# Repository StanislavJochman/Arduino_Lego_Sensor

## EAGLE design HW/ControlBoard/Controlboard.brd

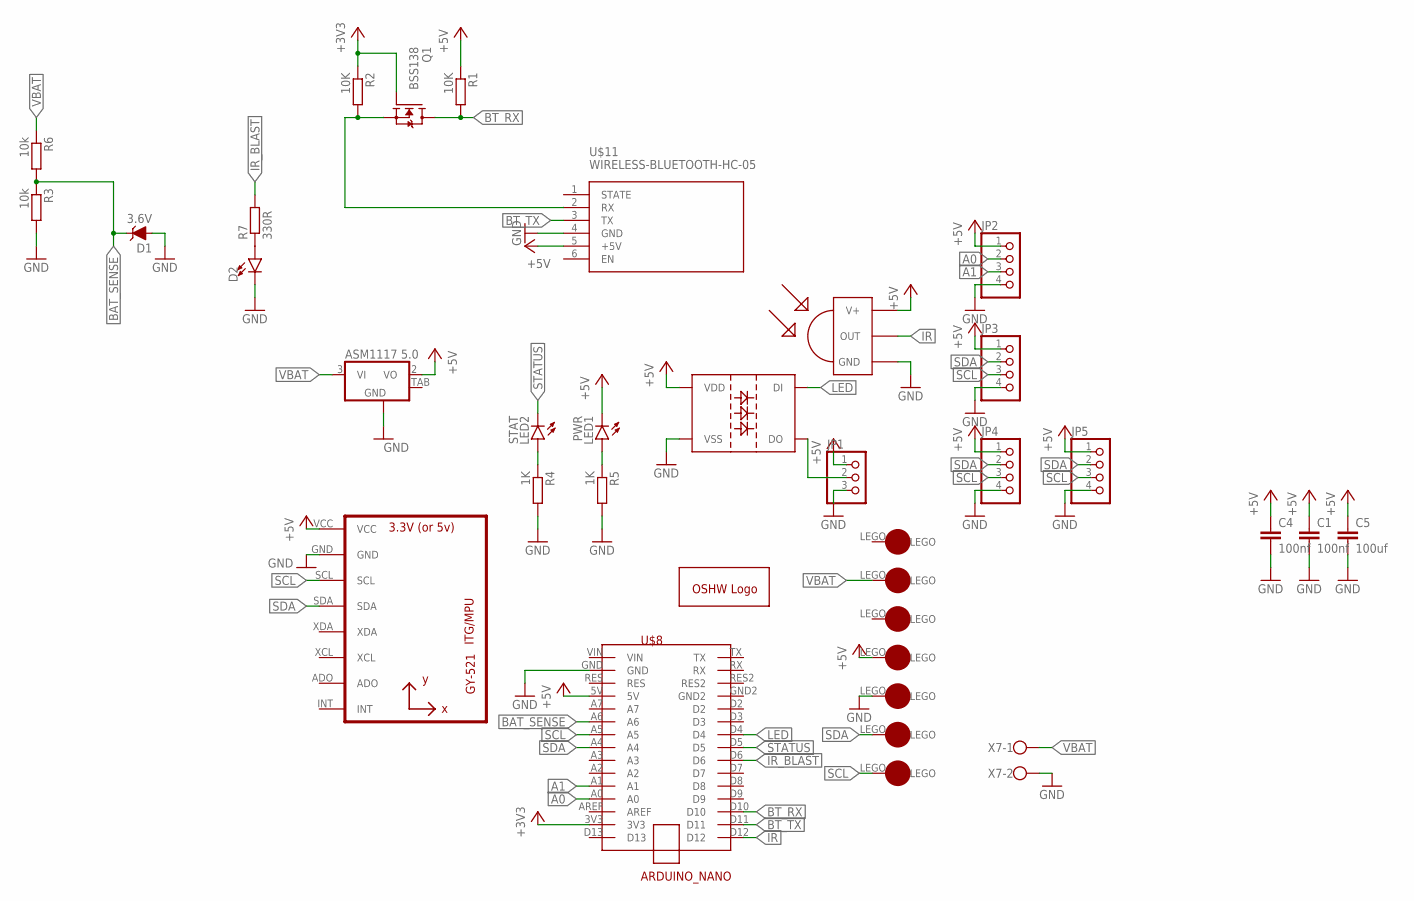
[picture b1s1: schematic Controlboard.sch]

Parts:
C1, C4: 100nf; C1206
C5: 100uf; C1206
D1: 3.6V; SOD-323
D2: LED5MM; LED_5MM
JP1: PINHD-1X3; 1X03
JP2, JP3, JP4, JP5: PINHD-1X4; 1X04
LED1: PWR; 1206
LED2: STAT; 1206
LED3: IND; WS2812B
Q1: BSS138; SOT23
R1, R2: 10K; M1206
R3, R6: 10k; M1206
R4, R5: 1K; M1206
R7: 330R; M1206
U1: MPU-6050MPU6050; MPU-6050
U$1, U$3, U$4, U$5, U$6, U$7, U$9: LEGO-1X1
U$2: OPENSOURCE; OSHW_5MM
U$8: ARDUINO_NANO; ARDUIN_NANO
U$10: TSOP4838; TSOP18XX
U$11: WIRELESS-BLUETOOTH-HC-05
U$12: ASM1117 5.0; LM1117
X7: W237-102

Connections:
+3V3: Q1.1 (G), R2.1, U$8.3V3
+5V: C1.1, C4.1, C5.1, JP1.1, JP2.1, JP3.1, JP4.1, JP5.1, LED1.C, LED3.1 (VDD), R1.1, U1.VCC, U$5.LEGO, U$8.5V, U$10.VCC (V+), U$11.5 (+5V), U$12.2 (VO)
A0: JP2.2, U$8.A0
A1: JP2.3, U$8.A1
BAT_SENSE: D1.C, R3.1, R6.2, U$8.A6
BT_RX: Q1.3 (D), R1.2, U$8.D10
BT_TX: U$8.D11, U$11.3 (TX)
GND: C1.2, C4.2, C5.2, D1.A, D2.K (C), JP1.3, JP2.4, JP3.4, JP4.4, JP5.4, LED3.3 (VSS), R3.2, R4.2, R5.2, U1.GND, U$4.LEGO, U$8.GND, U$10.GND, U$11.4 (GND), U$12.1 (GND), X7.2
IR: U$8.D12, U$10.OUT
IR_BLAST: R7.2, U$8.D6
LED: LED3.4 (DI), U$8.D4
unnamed: D2.A, R7.1
unnamed: Q1.2 (S), R2.2, U$11.2 (RX)
unnamed: LED2.A, R4.1
unnamed: LED1.A, R5.1
unnamed: JP1.2, LED3.2 (DO)
SCL: JP3.3, JP4.3, JP5.3, U1.SCL, U$1.LEGO, U$8.A5
SDA: JP3.2, JP4.2, JP5.2, U1.SDA, U$3.LEGO, U$8.A4
STATUS: LED2.C, U$8.D5
VBAT: R6.1, U$7.LEGO, U$12.3 (VI), X7.1

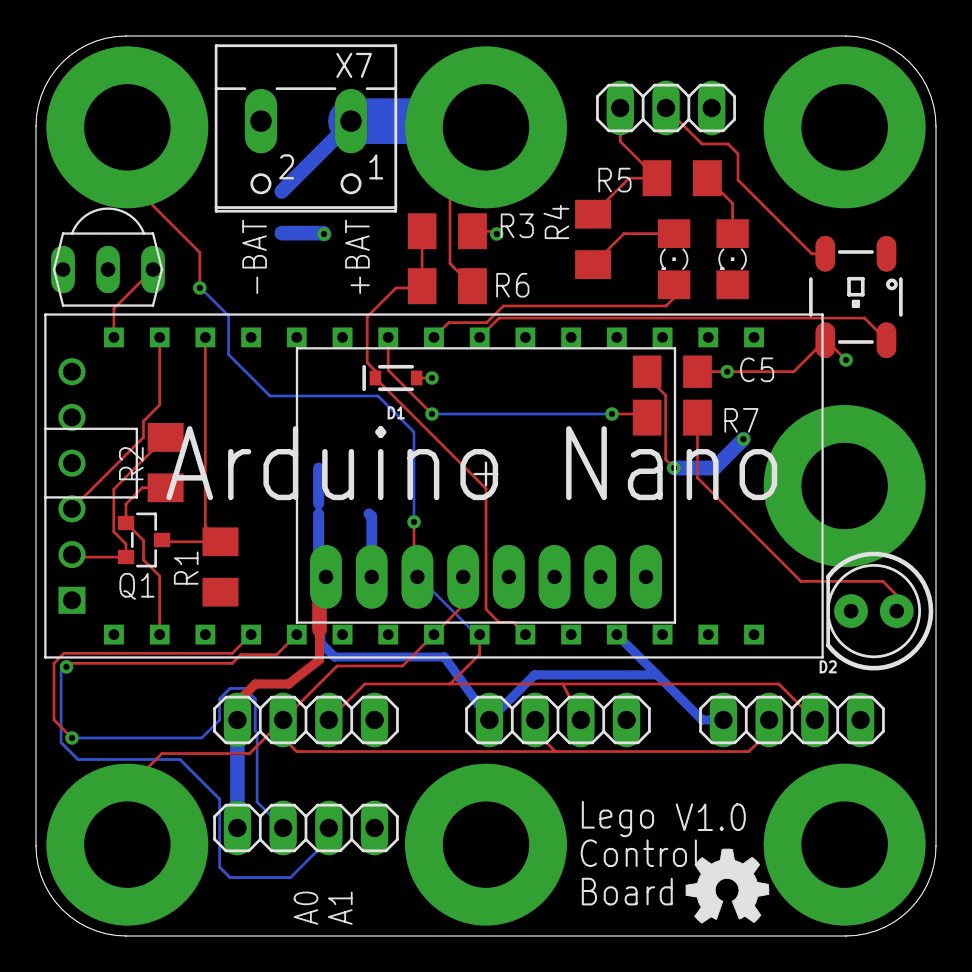
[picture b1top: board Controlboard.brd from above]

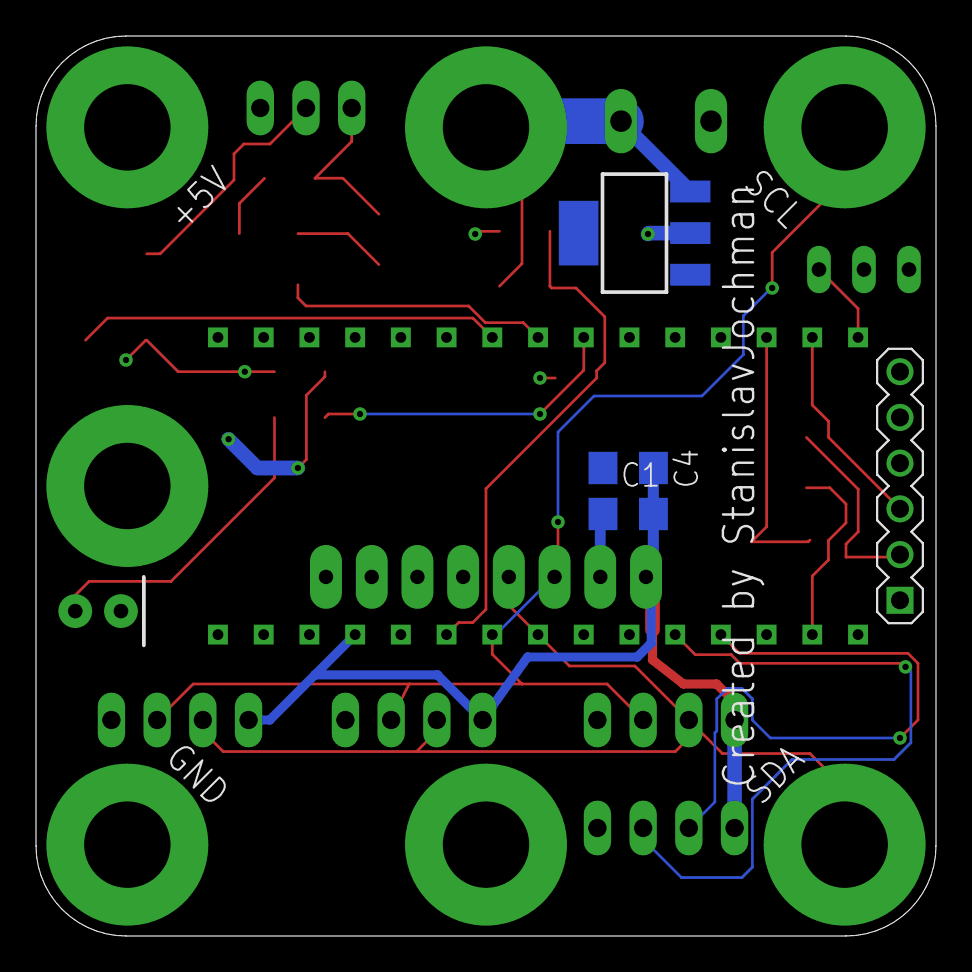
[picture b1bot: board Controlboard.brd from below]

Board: 2 copper layers, 50.0 x 50.0 mm, 35 parts (4 on the bottom side), 20 nets.

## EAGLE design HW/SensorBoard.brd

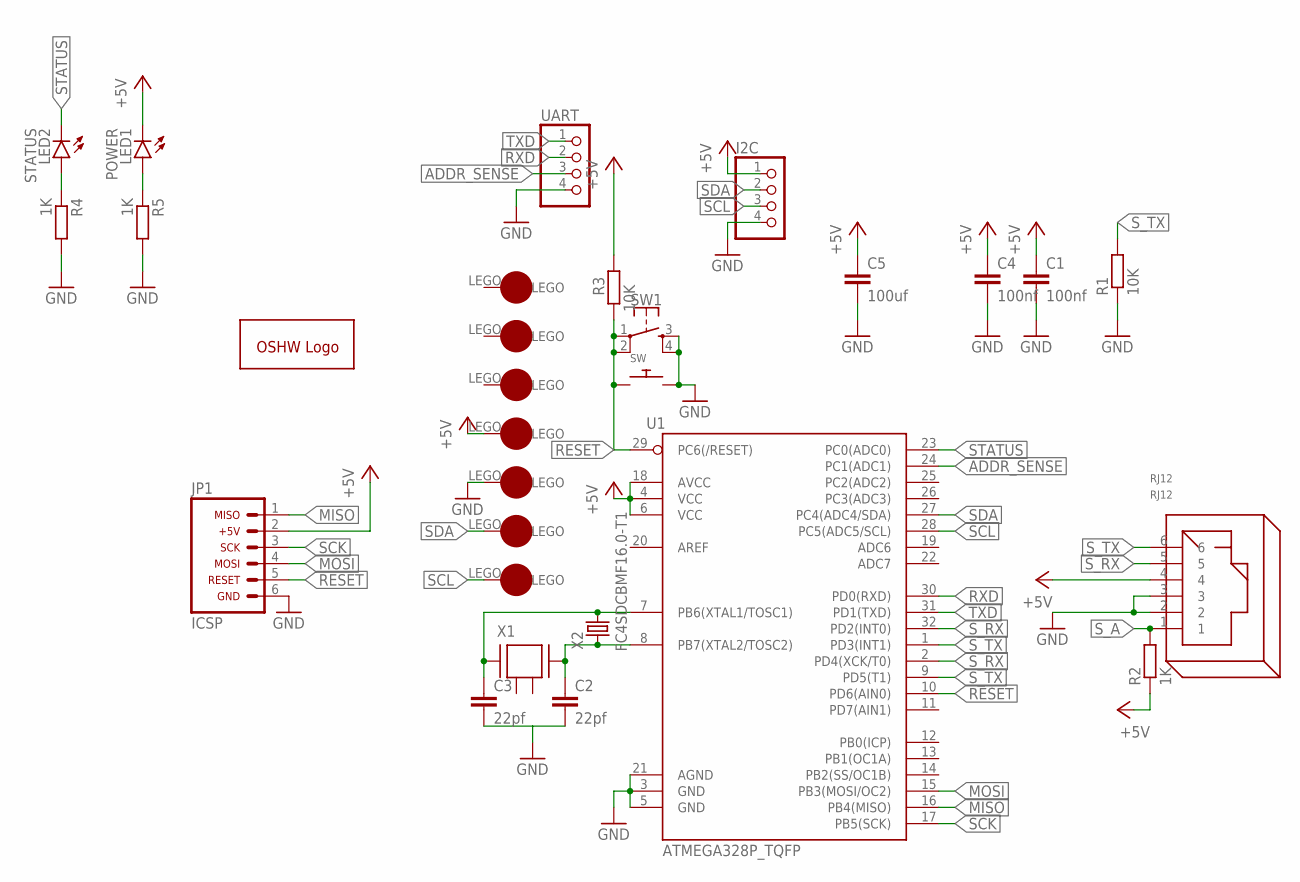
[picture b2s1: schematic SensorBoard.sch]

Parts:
C1, C4: 100nf; C1206
C2, C3: 22pf; C1206
C5: 100uf; C1206
I2C: PINHD-1X4; 1X04
JP1: ICSP_HEADER
LED1: POWER; 1206
LED2: STATUS; 1206
R1, R3: 10K; M1206
R2, R4, R5: 1K; M1206
RJ12: RJ12
SW: SWITCH_PUSHBUTTONC&K_KSS; BTN_CK_KSS
SW1: MOMENTARY-SWITCH-SPST-2-SMD-5.2MM; TACTILE_SWITCH_SMD_5.2MM
U1: ATMEGA328P_TQFP; TQFP32-08
U$1, U$3, U$4, U$5, U$6, U$7, U$9: LEGO-1X1
U$2: OPENSOURCE; OSHW_5MM
UART: PINHD-1X4; 1X04
X1: 7B-16.000MAAJ-T
X2: FC4SDCBMF16.0-T1

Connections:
+5V: C1.1, C4.1, C5.1, I2C.1, JP1.2, LED1.C, R2.1, R3.2, RJ12.4, U1.4 (VCC), U1.6 (VCC), U1.18 (AVCC), U$5.LEGO
ADDR_SENSE: U1.24 (PC1(ADC1)), UART.3
GND: C1.2, C2.2, C3.2, C4.2, C5.2, I2C.4, JP1.6, R1.1, R4.2, R5.2, RJ12.2, RJ12.3, SW.P$2, SW1.3, SW1.4, U1.3 (GND), U1.5 (GND), U1.21 (AGND), U$4.LEGO, UART.4
MISO: JP1.1, U1.16 (PB4(MISO))
MOSI: JP1.4, U1.15 (PB3(MOSI/OC2))
unnamed: C2.1, U1.8 (PB7(XTAL2/TOSC2)), X1.3, X2.1
unnamed: C3.1, U1.7 (PB6(XTAL1/TOSC1)), X1.1, X2.2
unnamed: LED2.A, R4.1
unnamed: LED1.A, R5.1
RESET: JP1.5, R3.1, SW.P$1, SW1.1, SW1.2, U1.10 (PD6(AIN0)), U1.29 (PC6(/RESET))
RXD: U1.30 (PD0(RXD)), UART.2
SCK: JP1.3, U1.17 (PB5(SCK))
SCL: I2C.3, U1.28 (PC5(ADC5/SCL)), U$1.LEGO
SDA: I2C.2, U1.27 (PC4(ADC4/SDA)), U$3.LEGO
STATUS: LED2.C, U1.23 (PC0(ADC0))
S_A: R2.2, RJ12.1
S_RX: RJ12.5, U1.2 (PD4(XCK/T0)), U1.32 (PD2(INT0))
S_TX: R1.2, RJ12.6, U1.1 (PD3(INT1)), U1.9 (PD5(T1))
TXD: U1.31 (PD1(TXD)), UART.1

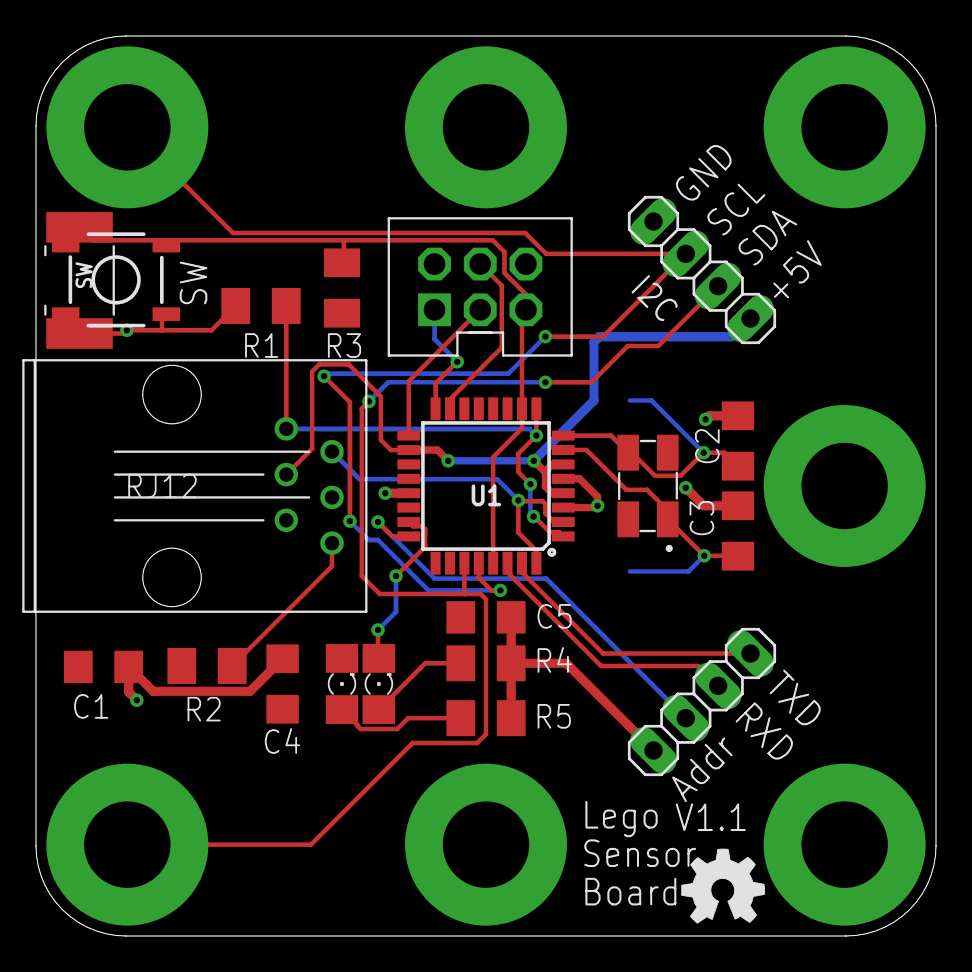
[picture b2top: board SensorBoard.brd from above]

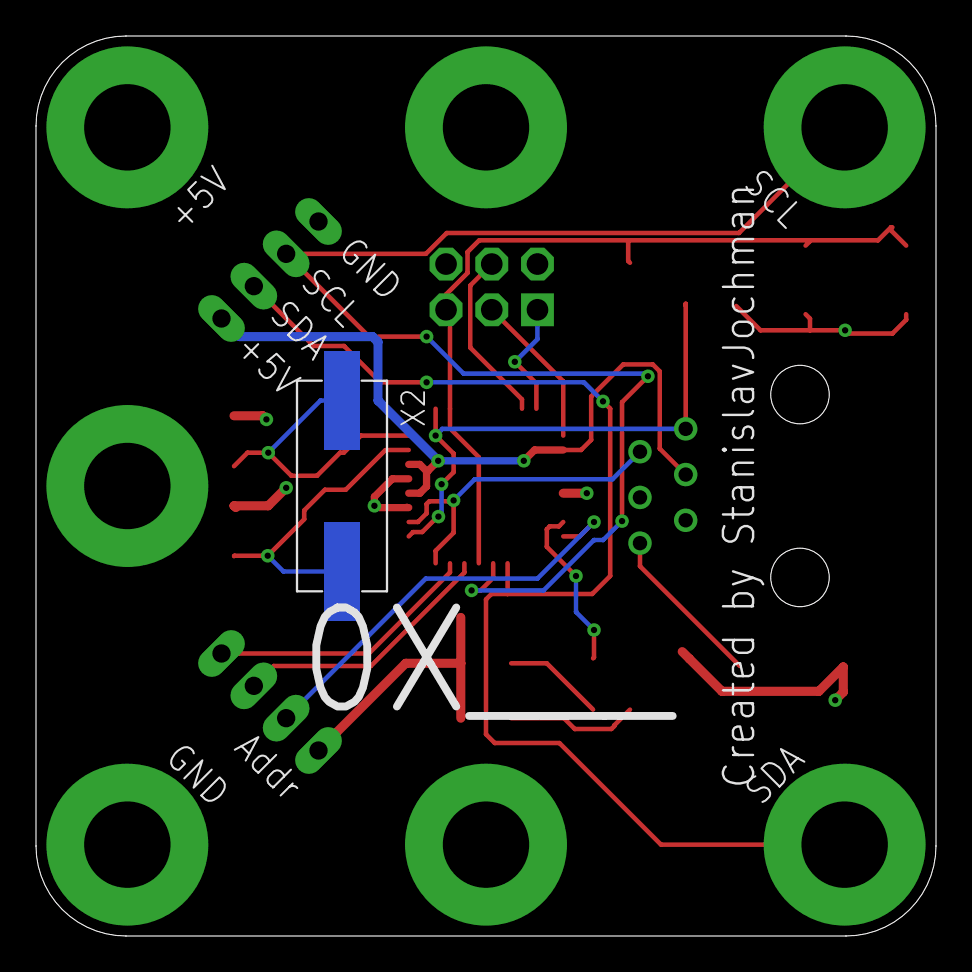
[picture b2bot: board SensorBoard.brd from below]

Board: 2 copper layers, 50.0 x 50.0 mm, 29 parts (2 on the bottom side), 19 nets.

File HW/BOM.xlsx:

Comment | Designator | Footprint | LCSC Part #（optional）
SW1 | SW1 | SMD-SW-4_5.1x5.1x2.0 | C318888
16mhz | X1 | SMD-3225_4P | C270482
1KΩ | R2,R4,R5 | 1206 | C4410
10KΩ | R1,R3 | 1206 | C17902
22pf | C2,C3 | 1206 | C313096
100nF | C1,C4 | 1206 | C24497
100uF | C5 | 1206 | C15008
Atmega328 | U1 | TQFP-32_7.0x7.0x0.8P | C14877
LED1 | LED1 | LED_1206 | C15595
LED2 | LED2 | LED_1206 | C72691

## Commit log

2018-12-08 basic functionality
2020-07-05 Working version
2020-07-09 working LS with BTN
2020-07-10 V1.0
2020-07-12 adding signalisation leds
2020-07-12 adding possibility to change I2C address
2020-07-12 fusion360 link
2020-07-28 adding control board

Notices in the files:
parts and their libraries:
SparkFun-DiscreteSemi: Licensing: Creative Commons ShareAlike 4.0 International - https://creativecommons.org/licenses/by-sa/4.0
